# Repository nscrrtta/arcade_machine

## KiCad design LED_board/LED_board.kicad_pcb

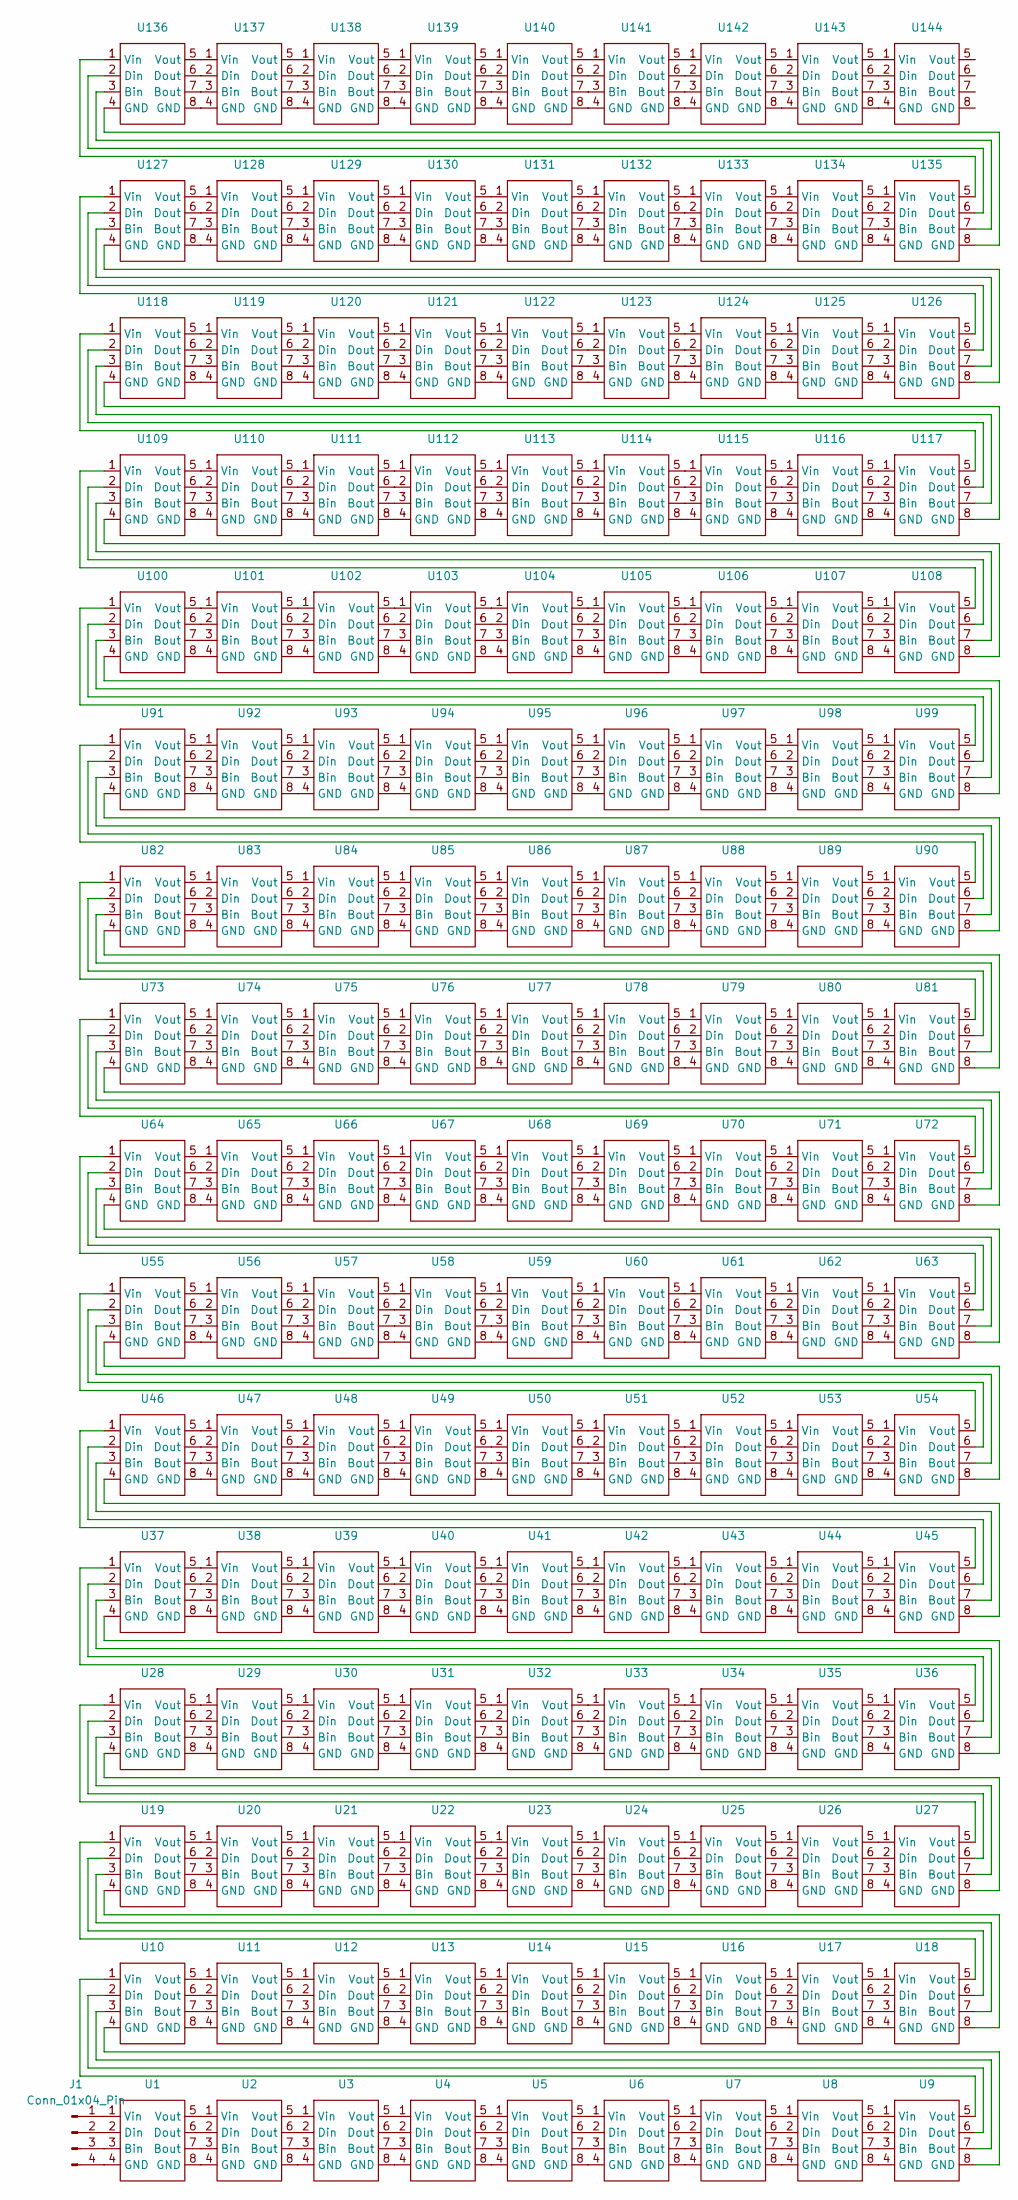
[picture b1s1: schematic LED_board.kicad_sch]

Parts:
J1: Conn_01x04_Pin; LED_connector
U1, U2, U3, U4, U5, U6, U7, U8, U9, U10, U11, U12, U13, U14, U15, U16, U17, U18, U19, U20, U21, U22, U23, U24, U25, U26, U27, U28, U29, U30, U31, U32, U33, U34, U35, U36, U37, U38, U39, U40, U41, U42, U43, U44, U45, U46, U47, U48, U49, U50, U51, U52, U53, U54, U55, U56, U57, U58, U59, U60, U61, U62, U63, U64, U65, U66, U67, U68, U69, U70, U71, U72, U73, U74, U75, U76, U77, U78, U79, U80, U81, U82, U83, U84, U85, U86, U87, U88, U89, U90, U91, U92, U93, U94, U95, U96, U97, U98, U99, U100, U101, U102, U103, U104, U105, U106, U107, U108, U109, U110, U111, U112, U113, U114, U115, U116, U117, U118, U119, U120, U121, U122, U123, U124, U125, U126, U127, U128, U129, U130, U131, U132, U133, U134, U135, U136, U137, U138, U139, U140, U141, U142, U143, U144: WS2185

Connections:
unnamed: J1.1, U1.1 (Vin)
unnamed: J1.2, U1.2 (Din)
unnamed: J1.3, U1.3 (Bin)
unnamed: J1.4, U1.4 (GND)
unnamed: U1.7 (Bout), U2.3 (Bin)
unnamed: U1.6 (Dout), U2.2 (Din)
unnamed: U1.8 (GND), U2.4 (GND)
unnamed: U1.5 (Vout), U2.1 (Vin)
unnamed: U2.7 (Bout), U3.3 (Bin)
unnamed: U2.6 (Dout), U3.2 (Din)
unnamed: U2.8 (GND), U3.4 (GND)
unnamed: U2.5 (Vout), U3.1 (Vin)
unnamed: U3.7 (Bout), U4.3 (Bin)
unnamed: U3.6 (Dout), U4.2 (Din)
unnamed: U3.8 (GND), U4.4 (GND)
unnamed: U3.5 (Vout), U4.1 (Vin)
unnamed: U4.7 (Bout), U5.3 (Bin)
unnamed: U4.6 (Dout), U5.2 (Din)
unnamed: U4.8 (GND), U5.4 (GND)
unnamed: U4.5 (Vout), U5.1 (Vin)
unnamed: U5.7 (Bout), U6.3 (Bin)
unnamed: U5.6 (Dout), U6.2 (Din)
unnamed: U5.8 (GND), U6.4 (GND)
unnamed: U5.5 (Vout), U6.1 (Vin)
unnamed: U6.7 (Bout), U7.3 (Bin)
unnamed: U6.6 (Dout), U7.2 (Din)
unnamed: U6.8 (GND), U7.4 (GND)
unnamed: U6.5 (Vout), U7.1 (Vin)
unnamed: U7.7 (Bout), U8.3 (Bin)
unnamed: U7.6 (Dout), U8.2 (Din)
unnamed: U7.8 (GND), U8.4 (GND)
unnamed: U7.5 (Vout), U8.1 (Vin)
unnamed: U8.7 (Bout), U9.3 (Bin)
unnamed: U8.6 (Dout), U9.2 (Din)
unnamed: U8.8 (GND), U9.4 (GND)
unnamed: U8.5 (Vout), U9.1 (Vin)
unnamed: U9.7 (Bout), U10.3 (Bin)
unnamed: U10.7 (Bout), U11.3 (Bin)
unnamed: U9.6 (Dout), U10.2 (Din)
unnamed: U10.6 (Dout), U11.2 (Din)
unnamed: U9.8 (GND), U10.4 (GND)
unnamed: U10.8 (GND), U11.4 (GND)
unnamed: U9.5 (Vout), U10.1 (Vin)
unnamed: U10.5 (Vout), U11.1 (Vin)
unnamed: U11.7 (Bout), U12.3 (Bin)
unnamed: U11.6 (Dout), U12.2 (Din)
unnamed: U11.8 (GND), U12.4 (GND)
unnamed: U11.5 (Vout), U12.1 (Vin)
unnamed: U12.7 (Bout), U13.3 (Bin)
unnamed: U12.6 (Dout), U13.2 (Din)
unnamed: U12.8 (GND), U13.4 (GND)
unnamed: U12.5 (Vout), U13.1 (Vin)
unnamed: U13.7 (Bout), U14.3 (Bin)
unnamed: U13.6 (Dout), U14.2 (Din)
unnamed: U13.8 (GND), U14.4 (GND)
unnamed: U13.5 (Vout), U14.1 (Vin)
unnamed: U14.7 (Bout), U15.3 (Bin)
unnamed: U14.6 (Dout), U15.2 (Din)
unnamed: U14.8 (GND), U15.4 (GND)
unnamed: U14.5 (Vout), U15.1 (Vin)
unnamed: U15.7 (Bout), U16.3 (Bin)
unnamed: U15.6 (Dout), U16.2 (Din)
unnamed: U15.8 (GND), U16.4 (GND)
unnamed: U15.5 (Vout), U16.1 (Vin)
unnamed: U16.7 (Bout), U17.3 (Bin)
unnamed: U16.6 (Dout), U17.2 (Din)
unnamed: U16.8 (GND), U17.4 (GND)
unnamed: U16.5 (Vout), U17.1 (Vin)
unnamed: U17.7 (Bout), U18.3 (Bin)
unnamed: U17.6 (Dout), U18.2 (Din)
unnamed: U17.8 (GND), U18.4 (GND)
unnamed: U17.5 (Vout), U18.1 (Vin)
unnamed: U18.7 (Bout), U19.3 (Bin)
unnamed: U18.6 (Dout), U19.2 (Din)
unnamed: U18.8 (GND), U19.4 (GND)
unnamed: U18.5 (Vout), U19.1 (Vin)
unnamed: U19.7 (Bout), U20.3 (Bin)
unnamed: U19.6 (Dout), U20.2 (Din)
unnamed: U19.8 (GND), U20.4 (GND)
unnamed: U19.5 (Vout), U20.1 (Vin)
unnamed: U20.7 (Bout), U21.3 (Bin)
unnamed: U20.6 (Dout), U21.2 (Din)
unnamed: U20.8 (GND), U21.4 (GND)
unnamed: U20.5 (Vout), U21.1 (Vin)
unnamed: U21.7 (Bout), U22.3 (Bin)
unnamed: U21.6 (Dout), U22.2 (Din)
unnamed: U21.8 (GND), U22.4 (GND)
unnamed: U21.5 (Vout), U22.1 (Vin)
unnamed: U22.7 (Bout), U23.3 (Bin)
unnamed: U22.6 (Dout), U23.2 (Din)
unnamed: U22.8 (GND), U23.4 (GND)
unnamed: U22.5 (Vout), U23.1 (Vin)
unnamed: U23.7 (Bout), U24.3 (Bin)
unnamed: U23.6 (Dout), U24.2 (Din)
unnamed: U23.8 (GND), U24.4 (GND)
unnamed: U23.5 (Vout), U24.1 (Vin)
unnamed: U24.7 (Bout), U25.3 (Bin)
unnamed: U24.6 (Dout), U25.2 (Din)
unnamed: U24.8 (GND), U25.4 (GND)
unnamed: U24.5 (Vout), U25.1 (Vin)
unnamed: U25.7 (Bout), U26.3 (Bin)
unnamed: U25.6 (Dout), U26.2 (Din)
unnamed: U25.8 (GND), U26.4 (GND)
unnamed: U25.5 (Vout), U26.1 (Vin)
unnamed: U26.7 (Bout), U27.3 (Bin)
unnamed: U26.6 (Dout), U27.2 (Din)
unnamed: U26.8 (GND), U27.4 (GND)
unnamed: U26.5 (Vout), U27.1 (Vin)
unnamed: U27.7 (Bout), U28.3 (Bin)
unnamed: U27.6 (Dout), U28.2 (Din)
unnamed: U27.8 (GND), U28.4 (GND)
unnamed: U27.5 (Vout), U28.1 (Vin)
unnamed: U28.7 (Bout), U29.3 (Bin)
unnamed: U28.6 (Dout), U29.2 (Din)
unnamed: U28.8 (GND), U29.4 (GND)
unnamed: U28.5 (Vout), U29.1 (Vin)
unnamed: U29.7 (Bout), U30.3 (Bin)
unnamed: U29.6 (Dout), U30.2 (Din)
unnamed: U29.8 (GND), U30.4 (GND)
unnamed: U29.5 (Vout), U30.1 (Vin)
unnamed: U30.7 (Bout), U31.3 (Bin)
unnamed: U30.6 (Dout), U31.2 (Din)
unnamed: U30.8 (GND), U31.4 (GND)
unnamed: U30.5 (Vout), U31.1 (Vin)
unnamed: U31.7 (Bout), U32.3 (Bin)
unnamed: U31.6 (Dout), U32.2 (Din)
unnamed: U31.8 (GND), U32.4 (GND)
unnamed: U31.5 (Vout), U32.1 (Vin)
unnamed: U32.7 (Bout), U33.3 (Bin)
unnamed: U32.6 (Dout), U33.2 (Din)
unnamed: U32.8 (GND), U33.4 (GND)
unnamed: U32.5 (Vout), U33.1 (Vin)
unnamed: U33.7 (Bout), U34.3 (Bin)
unnamed: U33.6 (Dout), U34.2 (Din)
unnamed: U33.8 (GND), U34.4 (GND)
unnamed: U33.5 (Vout), U34.1 (Vin)
unnamed: U34.7 (Bout), U35.3 (Bin)
unnamed: U34.6 (Dout), U35.2 (Din)
unnamed: U34.8 (GND), U35.4 (GND)
unnamed: U34.5 (Vout), U35.1 (Vin)
unnamed: U35.7 (Bout), U36.3 (Bin)
unnamed: U35.6 (Dout), U36.2 (Din)
unnamed: U35.8 (GND), U36.4 (GND)
unnamed: U35.5 (Vout), U36.1 (Vin)
unnamed: U36.7 (Bout), U37.3 (Bin)
unnamed: U36.6 (Dout), U37.2 (Din)
unnamed: U36.8 (GND), U37.4 (GND)
unnamed: U36.5 (Vout), U37.1 (Vin)
unnamed: U37.7 (Bout), U38.3 (Bin)
unnamed: U37.6 (Dout), U38.2 (Din)
unnamed: U37.8 (GND), U38.4 (GND)
unnamed: U37.5 (Vout), U38.1 (Vin)
unnamed: U38.7 (Bout), U39.3 (Bin)
unnamed: U38.6 (Dout), U39.2 (Din)
unnamed: U38.8 (GND), U39.4 (GND)
unnamed: U38.5 (Vout), U39.1 (Vin)
unnamed: U39.7 (Bout), U40.3 (Bin)
unnamed: U39.6 (Dout), U40.2 (Din)
unnamed: U39.8 (GND), U40.4 (GND)
unnamed: U39.5 (Vout), U40.1 (Vin)
unnamed: U40.7 (Bout), U41.3 (Bin)
unnamed: U40.6 (Dout), U41.2 (Din)
unnamed: U40.8 (GND), U41.4 (GND)
unnamed: U40.5 (Vout), U41.1 (Vin)
unnamed: U41.7 (Bout), U42.3 (Bin)
unnamed: U41.6 (Dout), U42.2 (Din)
unnamed: U41.8 (GND), U42.4 (GND)
unnamed: U41.5 (Vout), U42.1 (Vin)
unnamed: U42.7 (Bout), U43.3 (Bin)
unnamed: U42.6 (Dout), U43.2 (Din)
unnamed: U42.8 (GND), U43.4 (GND)
unnamed: U42.5 (Vout), U43.1 (Vin)
unnamed: U43.7 (Bout), U44.3 (Bin)
unnamed: U43.6 (Dout), U44.2 (Din)
unnamed: U43.8 (GND), U44.4 (GND)
unnamed: U43.5 (Vout), U44.1 (Vin)
unnamed: U44.7 (Bout), U45.3 (Bin)
unnamed: U44.6 (Dout), U45.2 (Din)
unnamed: U44.8 (GND), U45.4 (GND)
unnamed: U44.5 (Vout), U45.1 (Vin)
unnamed: U45.7 (Bout), U46.3 (Bin)
unnamed: U45.6 (Dout), U46.2 (Din)
unnamed: U45.8 (GND), U46.4 (GND)
unnamed: U45.5 (Vout), U46.1 (Vin)
unnamed: U46.7 (Bout), U47.3 (Bin)
unnamed: U46.6 (Dout), U47.2 (Din)
unnamed: U46.8 (GND), U47.4 (GND)
unnamed: U46.5 (Vout), U47.1 (Vin)
unnamed: U47.7 (Bout), U48.3 (Bin)
unnamed: U47.6 (Dout), U48.2 (Din)
unnamed: U47.8 (GND), U48.4 (GND)
unnamed: U47.5 (Vout), U48.1 (Vin)
unnamed: U48.7 (Bout), U49.3 (Bin)
unnamed: U48.6 (Dout), U49.2 (Din)
unnamed: U48.8 (GND), U49.4 (GND)
unnamed: U48.5 (Vout), U49.1 (Vin)
unnamed: U49.7 (Bout), U50.3 (Bin)
unnamed: U49.6 (Dout), U50.2 (Din)
unnamed: U49.8 (GND), U50.4 (GND)
unnamed: U49.5 (Vout), U50.1 (Vin)
unnamed: U50.7 (Bout), U51.3 (Bin)
unnamed: U50.6 (Dout), U51.2 (Din)
unnamed: U50.8 (GND), U51.4 (GND)
unnamed: U50.5 (Vout), U51.1 (Vin)
unnamed: U51.7 (Bout), U52.3 (Bin)
unnamed: U51.6 (Dout), U52.2 (Din)
unnamed: U51.8 (GND), U52.4 (GND)
unnamed: U51.5 (Vout), U52.1 (Vin)
unnamed: U52.7 (Bout), U53.3 (Bin)
unnamed: U52.6 (Dout), U53.2 (Din)
unnamed: U52.8 (GND), U53.4 (GND)
unnamed: U52.5 (Vout), U53.1 (Vin)
unnamed: U53.7 (Bout), U54.3 (Bin)
unnamed: U53.6 (Dout), U54.2 (Din)
unnamed: U53.8 (GND), U54.4 (GND)
unnamed: U53.5 (Vout), U54.1 (Vin)
unnamed: U54.7 (Bout), U55.3 (Bin)
unnamed: U54.6 (Dout), U55.2 (Din)
unnamed: U54.8 (GND), U55.4 (GND)
unnamed: U54.5 (Vout), U55.1 (Vin)
unnamed: U55.7 (Bout), U56.3 (Bin)
unnamed: U55.6 (Dout), U56.2 (Din)
unnamed: U55.8 (GND), U56.4 (GND)
unnamed: U55.5 (Vout), U56.1 (Vin)
unnamed: U56.7 (Bout), U57.3 (Bin)
unnamed: U56.6 (Dout), U57.2 (Din)
unnamed: U56.8 (GND), U57.4 (GND)
unnamed: U56.5 (Vout), U57.1 (Vin)
unnamed: U57.7 (Bout), U58.3 (Bin)
unnamed: U57.6 (Dout), U58.2 (Din)
unnamed: U57.8 (GND), U58.4 (GND)
unnamed: U57.5 (Vout), U58.1 (Vin)
unnamed: U58.7 (Bout), U59.3 (Bin)
unnamed: U58.6 (Dout), U59.2 (Din)
unnamed: U58.8 (GND), U59.4 (GND)
unnamed: U58.5 (Vout), U59.1 (Vin)
unnamed: U59.7 (Bout), U60.3 (Bin)
unnamed: U59.6 (Dout), U60.2 (Din)
unnamed: U59.8 (GND), U60.4 (GND)
unnamed: U59.5 (Vout), U60.1 (Vin)
unnamed: U60.7 (Bout), U61.3 (Bin)
unnamed: U60.6 (Dout), U61.2 (Din)
unnamed: U60.8 (GND), U61.4 (GND)
unnamed: U60.5 (Vout), U61.1 (Vin)
unnamed: U61.7 (Bout), U62.3 (Bin)
unnamed: U61.6 (Dout), U62.2 (Din)
unnamed: U61.8 (GND), U62.4 (GND)
unnamed: U61.5 (Vout), U62.1 (Vin)
unnamed: U62.7 (Bout), U63.3 (Bin)
unnamed: U62.6 (Dout), U63.2 (Din)
unnamed: U62.8 (GND), U63.4 (GND)
unnamed: U62.5 (Vout), U63.1 (Vin)
unnamed: U63.7 (Bout), U64.3 (Bin)
unnamed: U63.6 (Dout), U64.2 (Din)
unnamed: U63.8 (GND), U64.4 (GND)
unnamed: U63.5 (Vout), U64.1 (Vin)
unnamed: U64.7 (Bout), U65.3 (Bin)
unnamed: U64.6 (Dout), U65.2 (Din)
unnamed: U64.8 (GND), U65.4 (GND)
unnamed: U64.5 (Vout), U65.1 (Vin)
unnamed: U65.7 (Bout), U66.3 (Bin)
unnamed: U65.6 (Dout), U66.2 (Din)
unnamed: U65.8 (GND), U66.4 (GND)
unnamed: U65.5 (Vout), U66.1 (Vin)
unnamed: U66.7 (Bout), U67.3 (Bin)
unnamed: U66.6 (Dout), U67.2 (Din)
unnamed: U66.8 (GND), U67.4 (GND)
unnamed: U66.5 (Vout), U67.1 (Vin)
unnamed: U67.7 (Bout), U68.3 (Bin)
unnamed: U67.6 (Dout), U68.2 (Din)
unnamed: U67.8 (GND), U68.4 (GND)
unnamed: U67.5 (Vout), U68.1 (Vin)
unnamed: U68.7 (Bout), U69.3 (Bin)
unnamed: U68.6 (Dout), U69.2 (Din)
unnamed: U68.8 (GND), U69.4 (GND)
unnamed: U68.5 (Vout), U69.1 (Vin)
unnamed: U69.7 (Bout), U70.3 (Bin)
unnamed: U69.6 (Dout), U70.2 (Din)
unnamed: U69.8 (GND), U70.4 (GND)
unnamed: U69.5 (Vout), U70.1 (Vin)
unnamed: U70.7 (Bout), U71.3 (Bin)
unnamed: U70.6 (Dout), U71.2 (Din)
unnamed: U70.8 (GND), U71.4 (GND)
unnamed: U70.5 (Vout), U71.1 (Vin)
unnamed: U71.7 (Bout), U72.3 (Bin)
unnamed: U71.6 (Dout), U72.2 (Din)
unnamed: U71.8 (GND), U72.4 (GND)
unnamed: U71.5 (Vout), U72.1 (Vin)
unnamed: U72.7 (Bout), U73.3 (Bin)
unnamed: U72.6 (Dout), U73.2 (Din)
unnamed: U72.8 (GND), U73.4 (GND)
unnamed: U72.5 (Vout), U73.1 (Vin)
unnamed: U73.7 (Bout), U74.3 (Bin)
unnamed: U73.6 (Dout), U74.2 (Din)
unnamed: U73.8 (GND), U74.4 (GND)
unnamed: U73.5 (Vout), U74.1 (Vin)
unnamed: U74.7 (Bout), U75.3 (Bin)
unnamed: U74.6 (Dout), U75.2 (Din)
unnamed: U74.8 (GND), U75.4 (GND)
unnamed: U74.5 (Vout), U75.1 (Vin)
unnamed: U75.7 (Bout), U76.3 (Bin)
unnamed: U75.6 (Dout), U76.2 (Din)
unnamed: U75.8 (GND), U76.4 (GND)
unnamed: U75.5 (Vout), U76.1 (Vin)
unnamed: U76.7 (Bout), U77.3 (Bin)
unnamed: U76.6 (Dout), U77.2 (Din)
unnamed: U76.8 (GND), U77.4 (GND)
unnamed: U76.5 (Vout), U77.1 (Vin)
unnamed: U77.7 (Bout), U78.3 (Bin)
unnamed: U77.6 (Dout), U78.2 (Din)
unnamed: U77.8 (GND), U78.4 (GND)
unnamed: U77.5 (Vout), U78.1 (Vin)
unnamed: U78.7 (Bout), U79.3 (Bin)
unnamed: U78.6 (Dout), U79.2 (Din)
unnamed: U78.8 (GND), U79.4 (GND)
unnamed: U78.5 (Vout), U79.1 (Vin)
unnamed: U79.7 (Bout), U80.3 (Bin)
unnamed: U79.6 (Dout), U80.2 (Din)
unnamed: U79.8 (GND), U80.4 (GND)
unnamed: U79.5 (Vout), U80.1 (Vin)
unnamed: U80.7 (Bout), U81.3 (Bin)
unnamed: U80.6 (Dout), U81.2 (Din)
unnamed: U80.8 (GND), U81.4 (GND)
unnamed: U80.5 (Vout), U81.1 (Vin)
unnamed: U81.7 (Bout), U82.3 (Bin)
unnamed: U81.6 (Dout), U82.2 (Din)
unnamed: U81.8 (GND), U82.4 (GND)
unnamed: U81.5 (Vout), U82.1 (Vin)
unnamed: U82.7 (Bout), U83.3 (Bin)
unnamed: U82.6 (Dout), U83.2 (Din)
unnamed: U82.8 (GND), U83.4 (GND)
unnamed: U82.5 (Vout), U83.1 (Vin)
unnamed: U83.7 (Bout), U84.3 (Bin)
unnamed: U83.6 (Dout), U84.2 (Din)
unnamed: U83.8 (GND), U84.4 (GND)
unnamed: U83.5 (Vout), U84.1 (Vin)
unnamed: U84.7 (Bout), U85.3 (Bin)
unnamed: U84.6 (Dout), U85.2 (Din)
unnamed: U84.8 (GND), U85.4 (GND)
unnamed: U84.5 (Vout), U85.1 (Vin)
unnamed: U85.7 (Bout), U86.3 (Bin)
unnamed: U85.6 (Dout), U86.2 (Din)
unnamed: U85.8 (GND), U86.4 (GND)
unnamed: U85.5 (Vout), U86.1 (Vin)
unnamed: U86.7 (Bout), U87.3 (Bin)
unnamed: U86.6 (Dout), U87.2 (Din)
unnamed: U86.8 (GND), U87.4 (GND)
unnamed: U86.5 (Vout), U87.1 (Vin)
unnamed: U87.7 (Bout), U88.3 (Bin)
unnamed: U87.6 (Dout), U88.2 (Din)
unnamed: U87.8 (GND), U88.4 (GND)
unnamed: U87.5 (Vout), U88.1 (Vin)
unnamed: U88.7 (Bout), U89.3 (Bin)
unnamed: U88.6 (Dout), U89.2 (Din)
unnamed: U88.8 (GND), U89.4 (GND)
unnamed: U88.5 (Vout), U89.1 (Vin)
unnamed: U89.7 (Bout), U90.3 (Bin)
unnamed: U89.6 (Dout), U90.2 (Din)
unnamed: U89.8 (GND), U90.4 (GND)
unnamed: U89.5 (Vout), U90.1 (Vin)
unnamed: U90.7 (Bout), U91.3 (Bin)
unnamed: U90.6 (Dout), U91.2 (Din)
unnamed: U90.8 (GND), U91.4 (GND)
unnamed: U90.5 (Vout), U91.1 (Vin)
unnamed: U91.7 (Bout), U92.3 (Bin)
unnamed: U91.6 (Dout), U92.2 (Din)
unnamed: U91.8 (GND), U92.4 (GND)
unnamed: U91.5 (Vout), U92.1 (Vin)
unnamed: U92.7 (Bout), U93.3 (Bin)
unnamed: U92.6 (Dout), U93.2 (Din)
unnamed: U92.8 (GND), U93.4 (GND)
unnamed: U92.5 (Vout), U93.1 (Vin)
unnamed: U93.7 (Bout), U94.3 (Bin)
unnamed: U93.6 (Dout), U94.2 (Din)
unnamed: U93.8 (GND), U94.4 (GND)
unnamed: U93.5 (Vout), U94.1 (Vin)
unnamed: U94.7 (Bout), U95.3 (Bin)
unnamed: U94.6 (Dout), U95.2 (Din)
unnamed: U94.8 (GND), U95.4 (GND)
unnamed: U94.5 (Vout), U95.1 (Vin)
unnamed: U95.7 (Bout), U96.3 (Bin)
unnamed: U95.6 (Dout), U96.2 (Din)
unnamed: U95.8 (GND), U96.4 (GND)
unnamed: U95.5 (Vout), U96.1 (Vin)
unnamed: U96.7 (Bout), U97.3 (Bin)
unnamed: U96.6 (Dout), U97.2 (Din)
unnamed: U96.8 (GND), U97.4 (GND)
unnamed: U96.5 (Vout), U97.1 (Vin)
unnamed: U97.7 (Bout), U98.3 (Bin)
unnamed: U97.6 (Dout), U98.2 (Din)
unnamed: U97.8 (GND), U98.4 (GND)
unnamed: U97.5 (Vout), U98.1 (Vin)
unnamed: U98.7 (Bout), U99.3 (Bin)
unnamed: U98.6 (Dout), U99.2 (Din)
unnamed: U98.8 (GND), U99.4 (GND)
unnamed: U98.5 (Vout), U99.1 (Vin)
unnamed: U99.7 (Bout), U100.3 (Bin)
unnamed: U100.7 (Bout), U101.3 (Bin)
unnamed: U99.6 (Dout), U100.2 (Din)
unnamed: U100.6 (Dout), U101.2 (Din)
unnamed: U99.8 (GND), U100.4 (GND)
unnamed: U100.8 (GND), U101.4 (GND)
unnamed: U99.5 (Vout), U100.1 (Vin)
unnamed: U100.5 (Vout), U101.1 (Vin)
unnamed: U101.7 (Bout), U102.3 (Bin)
unnamed: U101.6 (Dout), U102.2 (Din)
unnamed: U101.8 (GND), U102.4 (GND)
unnamed: U101.5 (Vout), U102.1 (Vin)
unnamed: U102.7 (Bout), U103.3 (Bin)
unnamed: U102.6 (Dout), U103.2 (Din)
unnamed: U102.8 (GND), U103.4 (GND)
unnamed: U102.5 (Vout), U103.1 (Vin)
unnamed: U103.7 (Bout), U104.3 (Bin)
unnamed: U103.6 (Dout), U104.2 (Din)
unnamed: U103.8 (GND), U104.4 (GND)
unnamed: U103.5 (Vout), U104.1 (Vin)
unnamed: U104.7 (Bout), U105.3 (Bin)
unnamed: U104.6 (Dout), U105.2 (Din)
unnamed: U104.8 (GND), U105.4 (GND)
unnamed: U104.5 (Vout), U105.1 (Vin)
unnamed: U105.7 (Bout), U106.3 (Bin)
unnamed: U105.6 (Dout), U106.2 (Din)
unnamed: U105.8 (GND), U106.4 (GND)
unnamed: U105.5 (Vout), U106.1 (Vin)
unnamed: U106.7 (Bout), U107.3 (Bin)
unnamed: U106.6 (Dout), U107.2 (Din)
unnamed: U106.8 (GND), U107.4 (GND)
unnamed: U106.5 (Vout), U107.1 (Vin)
unnamed: U107.7 (Bout), U108.3 (Bin)
unnamed: U107.6 (Dout), U108.2 (Din)
unnamed: U107.8 (GND), U108.4 (GND)
unnamed: U107.5 (Vout), U108.1 (Vin)
unnamed: U108.7 (Bout), U109.3 (Bin)
unnamed: U108.6 (Dout), U109.2 (Din)
unnamed: U108.8 (GND), U109.4 (GND)
unnamed: U108.5 (Vout), U109.1 (Vin)
unnamed: U109.7 (Bout), U110.3 (Bin)
unnamed: U109.6 (Dout), U110.2 (Din)
unnamed: U109.8 (GND), U110.4 (GND)
unnamed: U109.5 (Vout), U110.1 (Vin)
unnamed: U110.7 (Bout), U111.3 (Bin)
unnamed: U110.6 (Dout), U111.2 (Din)
unnamed: U110.8 (GND), U111.4 (GND)
unnamed: U110.5 (Vout), U111.1 (Vin)
unnamed: U111.7 (Bout), U112.3 (Bin)
unnamed: U111.6 (Dout), U112.2 (Din)
unnamed: U111.8 (GND), U112.4 (GND)
unnamed: U111.5 (Vout), U112.1 (Vin)
unnamed: U112.7 (Bout), U113.3 (Bin)
unnamed: U112.6 (Dout), U113.2 (Din)
unnamed: U112.8 (GND), U113.4 (GND)
unnamed: U112.5 (Vout), U113.1 (Vin)
unnamed: U113.7 (Bout), U114.3 (Bin)
unnamed: U113.6 (Dout), U114.2 (Din)
unnamed: U113.8 (GND), U114.4 (GND)
unnamed: U113.5 (Vout), U114.1 (Vin)
unnamed: U114.7 (Bout), U115.3 (Bin)
unnamed: U114.6 (Dout), U115.2 (Din)
unnamed: U114.8 (GND), U115.4 (GND)
unnamed: U114.5 (Vout), U115.1 (Vin)
unnamed: U115.7 (Bout), U116.3 (Bin)
unnamed: U115.6 (Dout), U116.2 (Din)
unnamed: U115.8 (GND), U116.4 (GND)
unnamed: U115.5 (Vout), U116.1 (Vin)
unnamed: U116.7 (Bout), U117.3 (Bin)
unnamed: U116.6 (Dout), U117.2 (Din)
unnamed: U116.8 (GND), U117.4 (GND)
unnamed: U116.5 (Vout), U117.1 (Vin)
unnamed: U117.7 (Bout), U118.3 (Bin)
unnamed: U117.6 (Dout), U118.2 (Din)
unnamed: U117.8 (GND), U118.4 (GND)
unnamed: U117.5 (Vout), U118.1 (Vin)
unnamed: U118.7 (Bout), U119.3 (Bin)
unnamed: U118.6 (Dout), U119.2 (Din)
unnamed: U118.8 (GND), U119.4 (GND)
unnamed: U118.5 (Vout), U119.1 (Vin)
unnamed: U119.7 (Bout), U120.3 (Bin)
unnamed: U119.6 (Dout), U120.2 (Din)
unnamed: U119.8 (GND), U120.4 (GND)
unnamed: U119.5 (Vout), U120.1 (Vin)
unnamed: U120.7 (Bout), U121.3 (Bin)
unnamed: U120.6 (Dout), U121.2 (Din)
unnamed: U120.8 (GND), U121.4 (GND)
unnamed: U120.5 (Vout), U121.1 (Vin)
unnamed: U121.7 (Bout), U122.3 (Bin)
unnamed: U121.6 (Dout), U122.2 (Din)
unnamed: U121.8 (GND), U122.4 (GND)
unnamed: U121.5 (Vout), U122.1 (Vin)
unnamed: U122.7 (Bout), U123.3 (Bin)
unnamed: U122.6 (Dout), U123.2 (Din)
unnamed: U122.8 (GND), U123.4 (GND)
unnamed: U122.5 (Vout), U123.1 (Vin)
unnamed: U123.7 (Bout), U124.3 (Bin)
unnamed: U123.6 (Dout), U124.2 (Din)
unnamed: U123.8 (GND), U124.4 (GND)
unnamed: U123.5 (Vout), U124.1 (Vin)
unnamed: U124.7 (Bout), U125.3 (Bin)
unnamed: U124.6 (Dout), U125.2 (Din)
unnamed: U124.8 (GND), U125.4 (GND)
unnamed: U124.5 (Vout), U125.1 (Vin)
unnamed: U125.7 (Bout), U126.3 (Bin)
unnamed: U125.6 (Dout), U126.2 (Din)
unnamed: U125.8 (GND), U126.4 (GND)
unnamed: U125.5 (Vout), U126.1 (Vin)
unnamed: U126.7 (Bout), U127.3 (Bin)
unnamed: U126.6 (Dout), U127.2 (Din)
unnamed: U126.8 (GND), U127.4 (GND)
unnamed: U126.5 (Vout), U127.1 (Vin)
unnamed: U127.7 (Bout), U128.3 (Bin)
unnamed: U127.6 (Dout), U128.2 (Din)
unnamed: U127.8 (GND), U128.4 (GND)
unnamed: U127.5 (Vout), U128.1 (Vin)
unnamed: U128.7 (Bout), U129.3 (Bin)
unnamed: U128.6 (Dout), U129.2 (Din)
unnamed: U128.8 (GND), U129.4 (GND)
unnamed: U128.5 (Vout), U129.1 (Vin)
unnamed: U129.7 (Bout), U130.3 (Bin)
unnamed: U129.6 (Dout), U130.2 (Din)
unnamed: U129.8 (GND), U130.4 (GND)
unnamed: U129.5 (Vout), U130.1 (Vin)
unnamed: U130.7 (Bout), U131.3 (Bin)
unnamed: U130.6 (Dout), U131.2 (Din)
unnamed: U130.8 (GND), U131.4 (GND)
unnamed: U130.5 (Vout), U131.1 (Vin)
unnamed: U131.7 (Bout), U132.3 (Bin)
unnamed: U131.6 (Dout), U132.2 (Din)
unnamed: U131.8 (GND), U132.4 (GND)
unnamed: U131.5 (Vout), U132.1 (Vin)
unnamed: U132.7 (Bout), U133.3 (Bin)
unnamed: U132.6 (Dout), U133.2 (Din)
unnamed: U132.8 (GND), U133.4 (GND)
unnamed: U132.5 (Vout), U133.1 (Vin)
unnamed: U133.7 (Bout), U134.3 (Bin)
unnamed: U133.6 (Dout), U134.2 (Din)
unnamed: U133.8 (GND), U134.4 (GND)
unnamed: U133.5 (Vout), U134.1 (Vin)
unnamed: U134.7 (Bout), U135.3 (Bin)
unnamed: U134.6 (Dout), U135.2 (Din)
unnamed: U134.8 (GND), U135.4 (GND)
unnamed: U134.5 (Vout), U135.1 (Vin)
unnamed: U135.7 (Bout), U136.3 (Bin)
unnamed: U135.6 (Dout), U136.2 (Din)
unnamed: U135.8 (GND), U136.4 (GND)
unnamed: U135.5 (Vout), U136.1 (Vin)
unnamed: U136.7 (Bout), U137.3 (Bin)
unnamed: U136.6 (Dout), U137.2 (Din)
unnamed: U136.8 (GND), U137.4 (GND)
unnamed: U136.5 (Vout), U137.1 (Vin)
unnamed: U137.7 (Bout), U138.3 (Bin)
unnamed: U137.6 (Dout), U138.2 (Din)
unnamed: U137.8 (GND), U138.4 (GND)
unnamed: U137.5 (Vout), U138.1 (Vin)
unnamed: U138.7 (Bout), U139.3 (Bin)
unnamed: U138.6 (Dout), U139.2 (Din)
unnamed: U138.8 (GND), U139.4 (GND)
unnamed: U138.5 (Vout), U139.1 (Vin)
unnamed: U139.7 (Bout), U140.3 (Bin)
unnamed: U139.6 (Dout), U140.2 (Din)
unnamed: U139.8 (GND), U140.4 (GND)
unnamed: U139.5 (Vout), U140.1 (Vin)
unnamed: U140.7 (Bout), U141.3 (Bin)
unnamed: U140.6 (Dout), U141.2 (Din)
unnamed: U140.8 (GND), U141.4 (GND)
unnamed: U140.5 (Vout), U141.1 (Vin)
unnamed: U141.7 (Bout), U142.3 (Bin)
unnamed: U141.6 (Dout), U142.2 (Din)
unnamed: U141.8 (GND), U142.4 (GND)
unnamed: U141.5 (Vout), U142.1 (Vin)
unnamed: U142.7 (Bout), U143.3 (Bin)
unnamed: U142.6 (Dout), U143.2 (Din)
unnamed: U142.8 (GND), U143.4 (GND)
unnamed: U142.5 (Vout), U143.1 (Vin)
unnamed: U143.7 (Bout), U144.3 (Bin)
unnamed: U143.6 (Dout), U144.2 (Din)
unnamed: U143.8 (GND), U144.4 (GND)
unnamed: U143.5 (Vout), U144.1 (Vin)

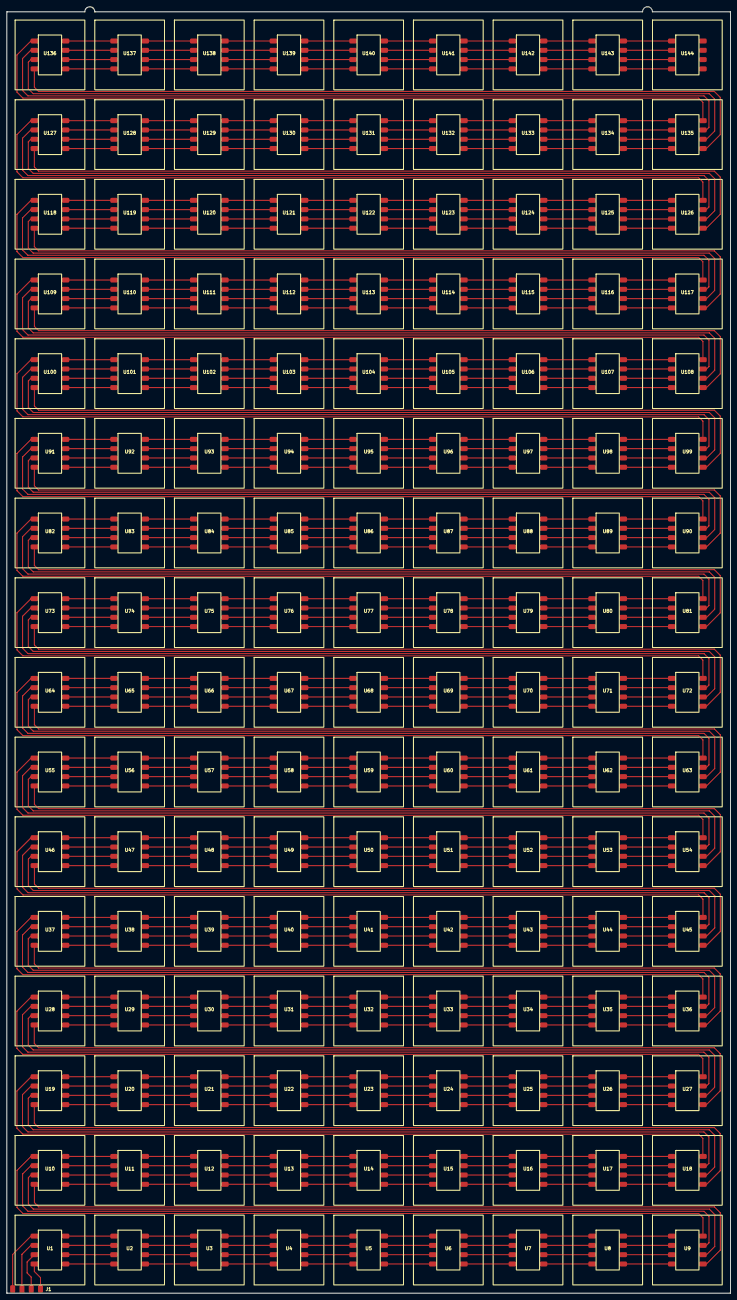
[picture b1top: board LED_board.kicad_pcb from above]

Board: 2 copper layers, 218.0 x 387.5 mm, 145 parts (0 on the bottom side), 576 nets.

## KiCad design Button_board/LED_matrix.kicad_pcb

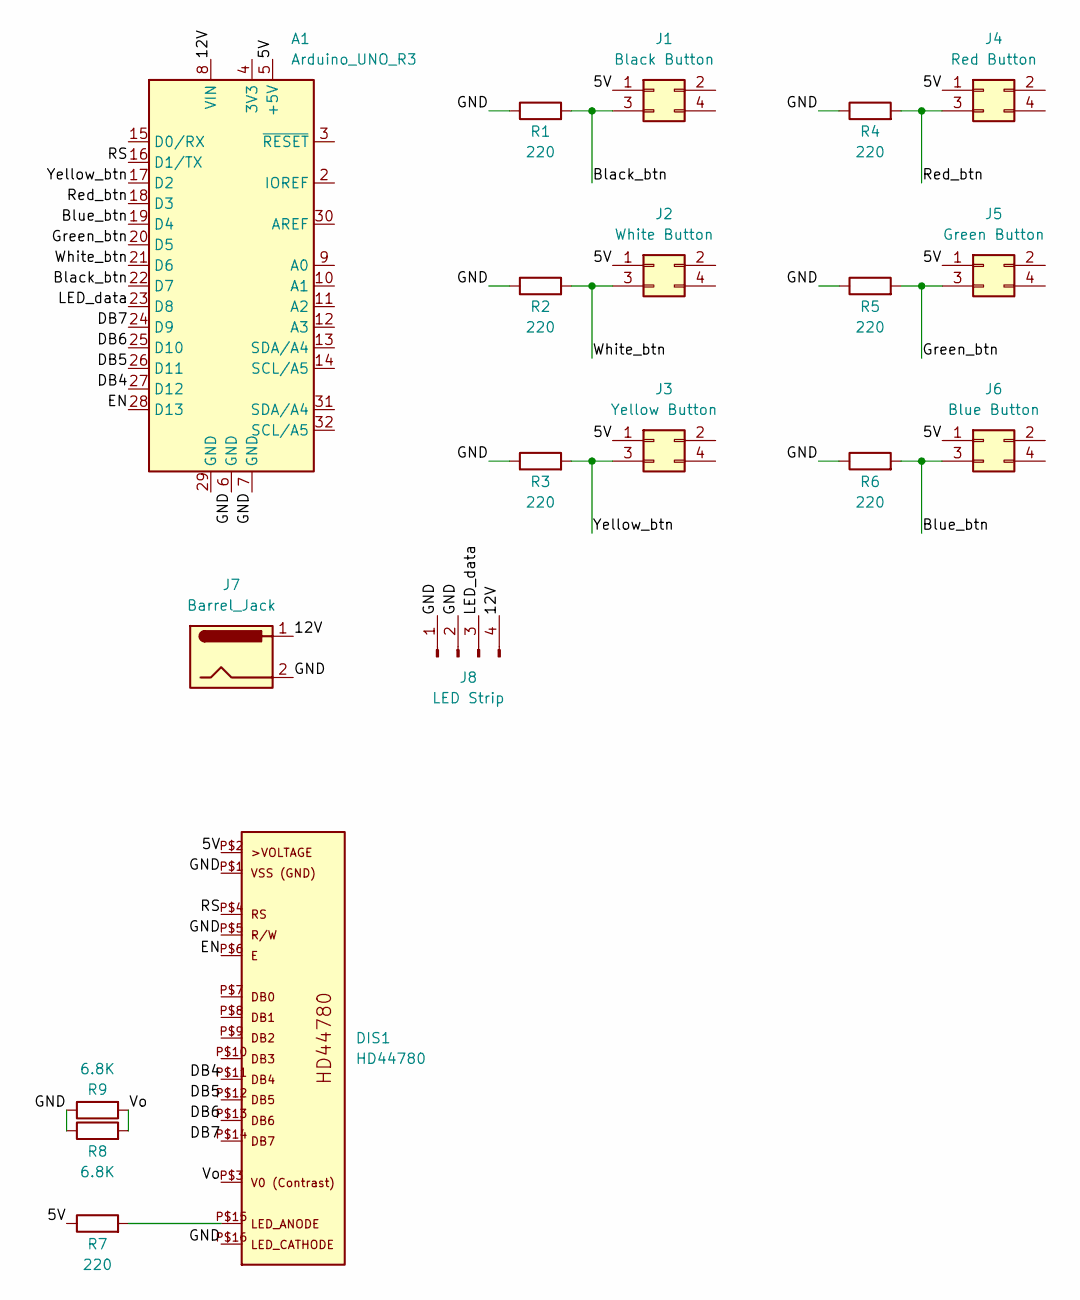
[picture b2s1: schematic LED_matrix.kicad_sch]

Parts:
A1: Arduino_UNO_R3
DIS1: HD44780; 16026-16X2; VOLTAGE 5V
J1: Black Button; led_matrix_button
J2: White Button; led_matrix_button
J3: Yellow Button; led_matrix_button
J4: Red Button; led_matrix_button
J5: Green Button; led_matrix_button
J6: Blue Button; led_matrix_button
J7: Barrel_Jack; BarrelJack_GCT_DCJ200-10-A_Horizontal
J8: LED Strip; PinHeader_1x04_P2.54mm_Vertical
R1, R2, R3, R4, R5, R6, R7: 220; resistor
R8, R9: 6.8K; resistor

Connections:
/5V: A1.5 (+5V), DIS1.P$2, J1.1, J2.1, J3.1, J4.1, J5.1, J6.1, R7.1
/12V: A1.8 (VIN), J7.1, J8.4
/Black_btn: A1.22 (D7), J1.3, R1.2
/Blue_btn: A1.19 (D4), J6.3, R6.2
/DB4: A1.27 (D12), DIS1.P$11
/DB5: A1.26 (D11), DIS1.P$12
/DB6: A1.25 (D10), DIS1.P$13
/DB7: A1.24 (D9), DIS1.P$14
/EN: A1.28 (D13), DIS1.P$6
/GND: A1.6 (GND), A1.7 (GND), DIS1.P$1, DIS1.P$5, DIS1.P$16, J7.2, J8.1, J8.2, R1.1, R2.1, R3.1, R4.1, R5.1, R6.1, R8.1, R9.1
/Green_btn: A1.20 (D5), J5.3, R5.2
/LED_data: A1.23 (D8), J8.3
/RS: A1.16 (D1/TX), DIS1.P$4
/Red_btn: A1.18 (D3), J4.3, R4.2
/Vo: DIS1.P$3, R8.2, R9.2
/White_btn: A1.21 (D6), J2.3, R2.2
/Yellow_btn: A1.17 (D2), J3.3, R3.2
unnamed: DIS1.P$15, R7.2

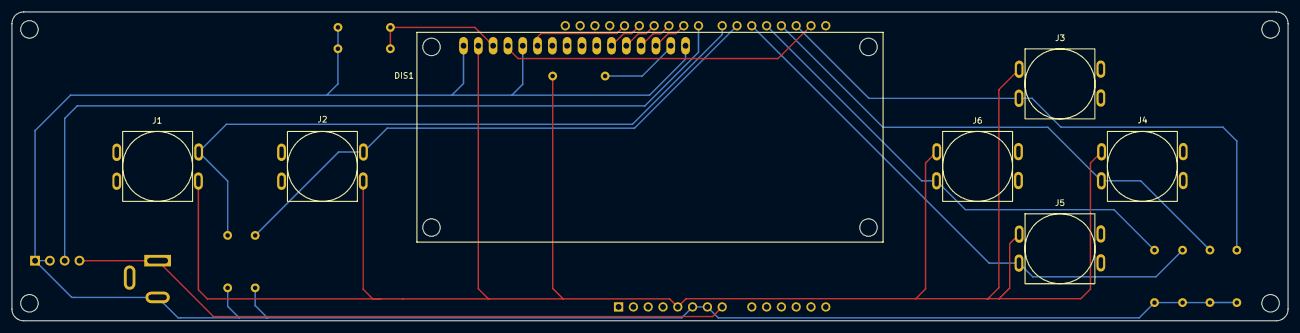
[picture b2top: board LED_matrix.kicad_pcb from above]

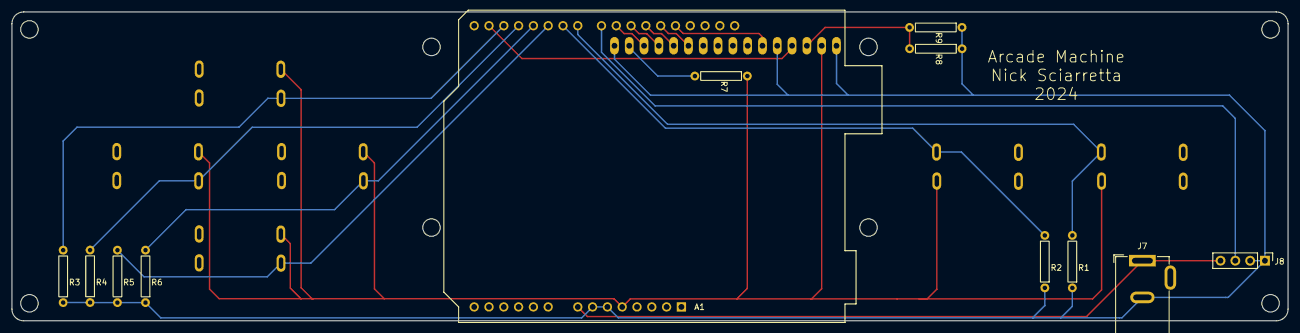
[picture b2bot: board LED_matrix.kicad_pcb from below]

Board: 2 copper layers, 219.0 x 53.0 mm, 19 parts (12 on the bottom side), 18 nets.
